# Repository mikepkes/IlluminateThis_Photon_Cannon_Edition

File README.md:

The Illuminate This "Photon Cannon Edition" is the 3rd production in the "Illuminate This" series.

Illuminate This boards are intended to be useful lighting boards for incorporating into your own projects.

Illuminate This boards are intended to provde:
* A large lighting area made of many LEDs
* Utilize component surplus at VHS
* Be easy to solder for people new to SMD components
* Customizable Lighitng, Remove Rows you don't want!

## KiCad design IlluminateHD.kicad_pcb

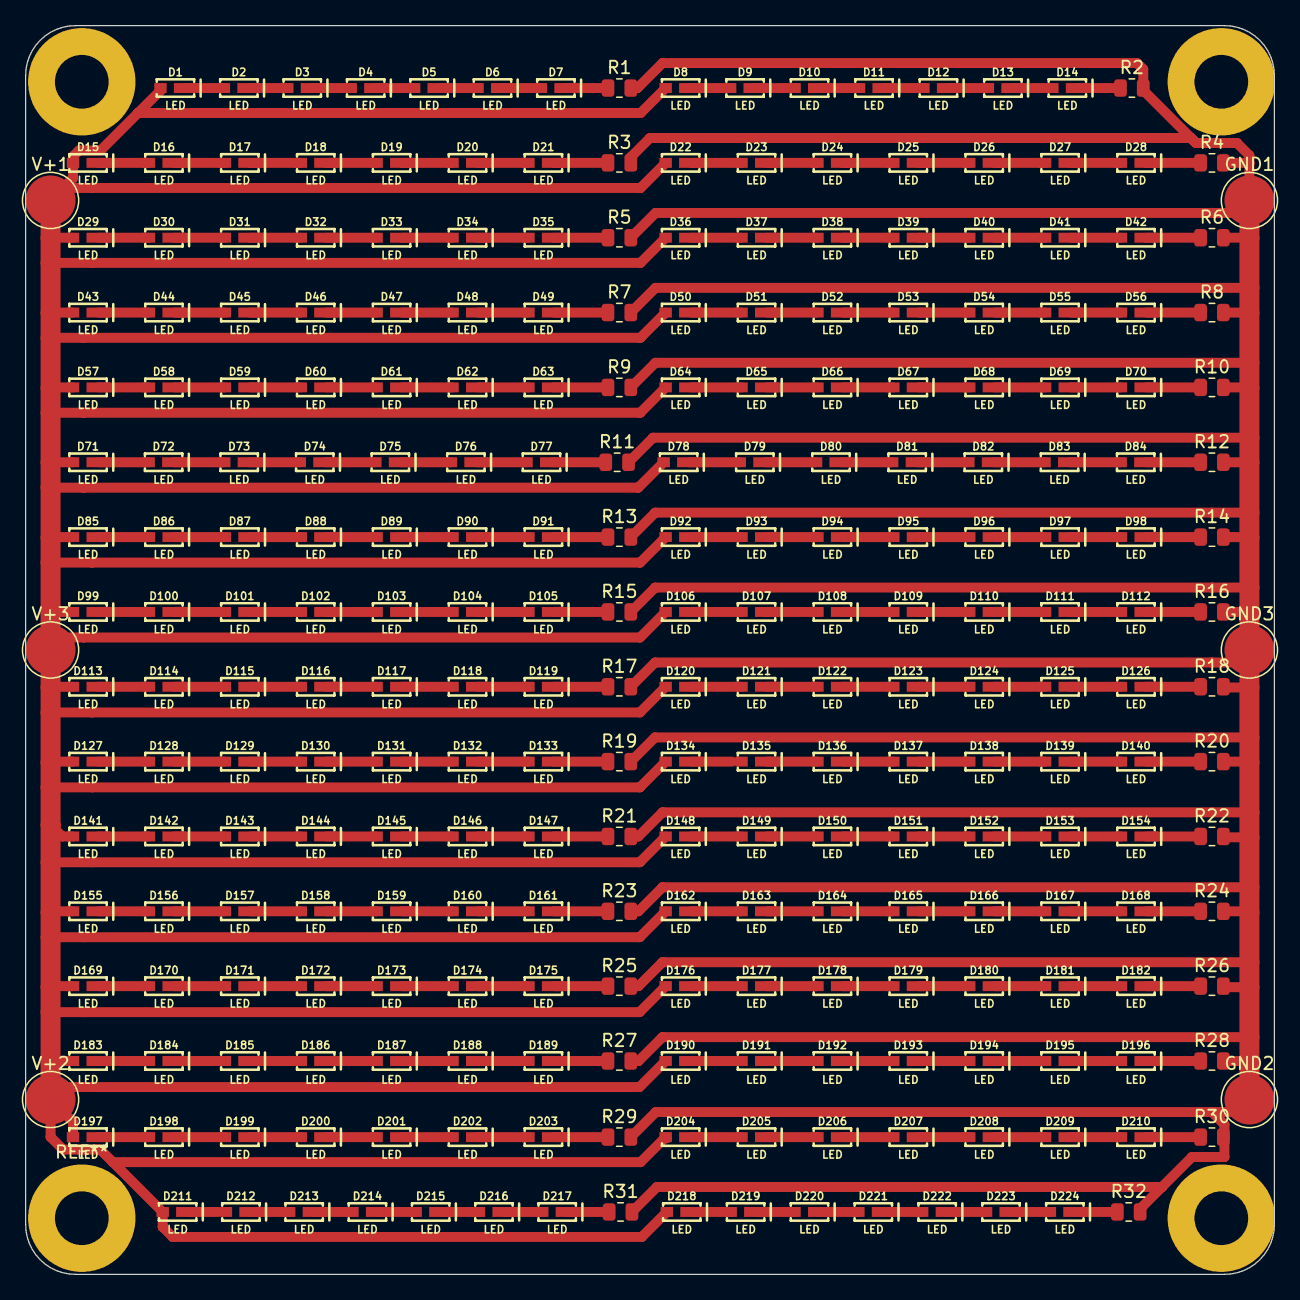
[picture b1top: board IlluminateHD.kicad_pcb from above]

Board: 2 copper layers, 100.0 x 100.0 mm, 262 parts (0 on the bottom side), 226 nets.

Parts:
D1, D2, D3, D4, D5, D6, D7, D8, D9, D10, D11, D12, D13, D14, D15, D16, D17, D18, D19, D20, D21, D22, D23, D24, D25, D26, D27, D28, D29, D30, D31, D32, D33, D34, D35, D36, D37, D38, D39, D40, D41, D42, D43, D44, D45, D46, D47, D48, D49, D50, D51, D52, D53, D54, D55, D56, D57, D58, D59, D60, D61, D62, D63, D64, D65, D66, D67, D68, D69, D70, D71, D72, D73, D74, D75, D76, D77, D78, D79, D80, D81, D82, D83, D84, D85, D86, D87, D88, D89, D90, D91, D92, D93, D94, D95, D96, D97, D98, D99, D100, D101, D102, D103, D104, D105, D106, D107, D108, D109, D110, D111, D112, D113, D114, D115, D116, D117, D118, D119, D120, D121, D122, D123, D124, D125, D126, D127, D128, D129, D130, D131, D132, D133, D134, D135, D136, D137, D138, D139, D140, D141, D142, D143, D144, D145, D146, D147, D148, D149, D150, D151, D152, D153, D154, D155, D156, D157, D158, D159, D160, D161, D162, D163, D164, D165, D166, D167, D168, D169, D170, D171, D172, D173, D174, D175, D176, D177, D178, D179, D180, D181, D182, D183, D184, D185, D186, D187, D188, D189, D190, D191, D192, D193, D194, D195, D196, D197, D198, D199, D200, D201, D202, D203, D204, D205, D206, D207, D208, D209, D210, D211, D212, D213, D214, D215, D216, D217, D218, D219, D220, D221, D222, D223, D224: LED; SUPER_BRIGHT_SMD_LED_3014
GND1, GND2, GND3: TestPoint; TestPoint_Pad_D4.0mm
R1, R2, R3, R4, R5, R6, R7, R8, R9, R10, R11, R12, R13, R14, R15, R16, R17, R18, R19, R20, R21, R22, R23, R24, R25, R26, R27, R28, R29, R30, R31, R32: R_US; R_0805_2012Metric
V+1, V+2, V+3: TestPoint; TestPoint_Pad_D4.0mm

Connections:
+24V: D1.A, D8.A, D15.A, D22.A, D29.A, D36.A, D43.A, D50.A, D57.A, D64.A, D71.A, D78.A, D85.A, D92.A, D99.A, D106.A, D113.A, D120.A, D127.A, D134.A, D141.A, D148.A, D155.A, D162.A, D169.A, D176.A, D183.A, D190.A, D197.A, D204.A, D211.A, D218.A, V+1.1, V+2.1, V+3.1
GND: GND1.1, GND2.1, GND3.1, R1.2, R2.2, R3.2, R4.2, R5.2, R6.2, R7.2, R8.2, R9.2, R10.2, R11.2, R12.2, R13.2, R14.2, R15.2, R16.2, R17.2, R18.2, R19.2, R20.2, R21.2, R22.2, R23.2, R24.2, R25.2, R26.2, R27.2, R28.2, R29.2, R30.2, R31.2, R32.2
unnamed: D1.C, D2.A
unnamed: D2.C, D3.A
unnamed: D3.C, D4.A
unnamed: D4.C, D5.A
unnamed: D5.C, D6.A
unnamed: D6.C, D7.A
unnamed: D7.C, R1.1
unnamed: D8.C, D9.A
unnamed: D9.C, D10.A
unnamed: D10.C, D11.A
unnamed: D11.C, D12.A
unnamed: D12.C, D13.A
unnamed: D13.C, D14.A
unnamed: D14.C, R2.1
unnamed: D15.C, D16.A
unnamed: D16.C, D17.A
unnamed: D17.C, D18.A
unnamed: D18.C, D19.A
unnamed: D19.C, D20.A
unnamed: D20.C, D21.A
unnamed: D21.C, R3.1
unnamed: D22.C, D23.A
unnamed: D23.C, D24.A
unnamed: D24.C, D25.A
unnamed: D25.C, D26.A
unnamed: D26.C, D27.A
unnamed: D27.C, D28.A
unnamed: D28.C, R4.1
unnamed: D29.C, D30.A
unnamed: D30.C, D31.A
unnamed: D31.C, D32.A
unnamed: D32.C, D33.A
unnamed: D33.C, D34.A
unnamed: D34.C, D35.A
unnamed: D35.C, R5.1
unnamed: D36.C, D37.A
unnamed: D37.C, D38.A
unnamed: D38.C, D39.A
unnamed: D39.C, D40.A
unnamed: D40.C, D41.A
unnamed: D41.C, D42.A
unnamed: D42.C, R6.1
unnamed: D43.C, D44.A
unnamed: D44.C, D45.A
unnamed: D45.C, D46.A
unnamed: D46.C, D47.A
unnamed: D47.C, D48.A
unnamed: D48.C, D49.A
unnamed: D49.C, R7.1
unnamed: D50.C, D51.A
unnamed: D51.C, D52.A
unnamed: D52.C, D53.A
unnamed: D53.C, D54.A
unnamed: D54.C, D55.A
unnamed: D55.C, D56.A
unnamed: D56.C, R8.1
unnamed: D57.C, D58.A
unnamed: D58.C, D59.A
unnamed: D59.C, D60.A
unnamed: D60.C, D61.A
unnamed: D61.C, D62.A
unnamed: D62.C, D63.A
unnamed: D63.C, R9.1
unnamed: D64.C, D65.A
unnamed: D65.C, D66.A
unnamed: D66.C, D67.A
unnamed: D67.C, D68.A
unnamed: D68.C, D69.A
unnamed: D69.C, D70.A
unnamed: D70.C, R10.1
unnamed: D71.C, D72.A
unnamed: D72.C, D73.A
unnamed: D73.C, D74.A
unnamed: D74.C, D75.A
unnamed: D75.C, D76.A
unnamed: D76.C, D77.A
unnamed: D77.C, R11.1
unnamed: D78.C, D79.A
unnamed: D79.C, D80.A
unnamed: D80.C, D81.A
unnamed: D81.C, D82.A
unnamed: D82.C, D83.A
unnamed: D83.C, D84.A
unnamed: D84.C, R12.1
unnamed: D85.C, D86.A
unnamed: D86.C, D87.A
unnamed: D87.C, D88.A
unnamed: D88.C, D89.A
unnamed: D89.C, D90.A
unnamed: D90.C, D91.A
unnamed: D91.C, R13.1
unnamed: D92.C, D93.A
unnamed: D93.C, D94.A
unnamed: D94.C, D95.A
unnamed: D95.C, D96.A
unnamed: D96.C, D97.A
unnamed: D97.C, D98.A
unnamed: D98.C, R14.1
unnamed: D99.C, D100.A
unnamed: D100.C, D101.A
unnamed: D101.C, D102.A
unnamed: D102.C, D103.A
unnamed: D103.C, D104.A
unnamed: D104.C, D105.A
unnamed: D105.C, R15.1
unnamed: D106.C, D107.A
unnamed: D107.C, D108.A
unnamed: D108.C, D109.A
unnamed: D109.C, D110.A
unnamed: D110.C, D111.A
unnamed: D111.C, D112.A
unnamed: D112.C, R16.1
unnamed: D113.C, D114.A
unnamed: D114.C, D115.A
unnamed: D115.C, D116.A
unnamed: D116.C, D117.A
unnamed: D117.C, D118.A
unnamed: D118.C, D119.A
unnamed: D119.C, R17.1
unnamed: D120.C, D121.A
unnamed: D121.C, D122.A
unnamed: D122.C, D123.A
unnamed: D123.C, D124.A
unnamed: D124.C, D125.A
unnamed: D125.C, D126.A
unnamed: D126.C, R18.1
unnamed: D127.C, D128.A
unnamed: D128.C, D129.A
unnamed: D129.C, D130.A
unnamed: D130.C, D131.A
unnamed: D131.C, D132.A
unnamed: D132.C, D133.A
unnamed: D133.C, R19.1
unnamed: D134.C, D135.A
unnamed: D135.C, D136.A
unnamed: D136.C, D137.A
unnamed: D137.C, D138.A
unnamed: D138.C, D139.A
unnamed: D139.C, D140.A
unnamed: D140.C, R20.1
unnamed: D141.C, D142.A
unnamed: D142.C, D143.A
unnamed: D143.C, D144.A
unnamed: D144.C, D145.A
unnamed: D145.C, D146.A
unnamed: D146.C, D147.A
unnamed: D147.C, R21.1
unnamed: D148.C, D149.A
unnamed: D149.C, D150.A
unnamed: D150.C, D151.A
unnamed: D151.C, D152.A
unnamed: D152.C, D153.A
unnamed: D153.C, D154.A
unnamed: D154.C, R22.1
unnamed: D155.C, D156.A
unnamed: D156.C, D157.A
unnamed: D157.C, D158.A
unnamed: D158.C, D159.A
unnamed: D159.C, D160.A
unnamed: D160.C, D161.A
unnamed: D161.C, R23.1
unnamed: D162.C, D163.A
unnamed: D163.C, D164.A
unnamed: D164.C, D165.A
unnamed: D165.C, D166.A
unnamed: D166.C, D167.A
unnamed: D167.C, D168.A
unnamed: D168.C, R24.1
unnamed: D169.C, D170.A
unnamed: D170.C, D171.A
unnamed: D171.C, D172.A
unnamed: D172.C, D173.A
unnamed: D173.C, D174.A
unnamed: D174.C, D175.A
unnamed: D175.C, R25.1
unnamed: D176.C, D177.A
unnamed: D177.C, D178.A
unnamed: D178.C, D179.A
unnamed: D179.C, D180.A
unnamed: D180.C, D181.A
unnamed: D181.C, D182.A
unnamed: D182.C, R26.1
unnamed: D183.C, D184.A
unnamed: D184.C, D185.A
unnamed: D185.C, D186.A
unnamed: D186.C, D187.A
unnamed: D187.C, D188.A
unnamed: D188.C, D189.A
unnamed: D189.C, R27.1
unnamed: D190.C, D191.A
unnamed: D191.C, D192.A
unnamed: D192.C, D193.A
unnamed: D193.C, D194.A
unnamed: D194.C, D195.A
unnamed: D195.C, D196.A
unnamed: D196.C, R28.1
unnamed: D197.C, D198.A
unnamed: D198.C, D199.A
unnamed: D199.C, D200.A
unnamed: D200.C, D201.A
unnamed: D201.C, D202.A
unnamed: D202.C, D203.A
unnamed: D203.C, R29.1
unnamed: D204.C, D205.A
unnamed: D205.C, D206.A
unnamed: D206.C, D207.A
unnamed: D207.C, D208.A
unnamed: D208.C, D209.A
unnamed: D209.C, D210.A
unnamed: D210.C, R30.1
unnamed: D211.C, D212.A
unnamed: D212.C, D213.A
unnamed: D213.C, D214.A
unnamed: D214.C, D215.A
unnamed: D215.C, D216.A
unnamed: D216.C, D217.A
unnamed: D217.C, R31.1
unnamed: D218.C, D219.A
unnamed: D219.C, D220.A
unnamed: D220.C, D221.A
unnamed: D221.C, D222.A
unnamed: D222.C, D223.A
unnamed: D223.C, D224.A
unnamed: D224.C, R32.1

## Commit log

2022-02-02 Initial Commit, v3.0
2022-02-02 Added README
2022-02-02 Create LICENSE
    Add license file.
2022-05-15 getting ready for release.
2022-05-15 First pass at manual.
